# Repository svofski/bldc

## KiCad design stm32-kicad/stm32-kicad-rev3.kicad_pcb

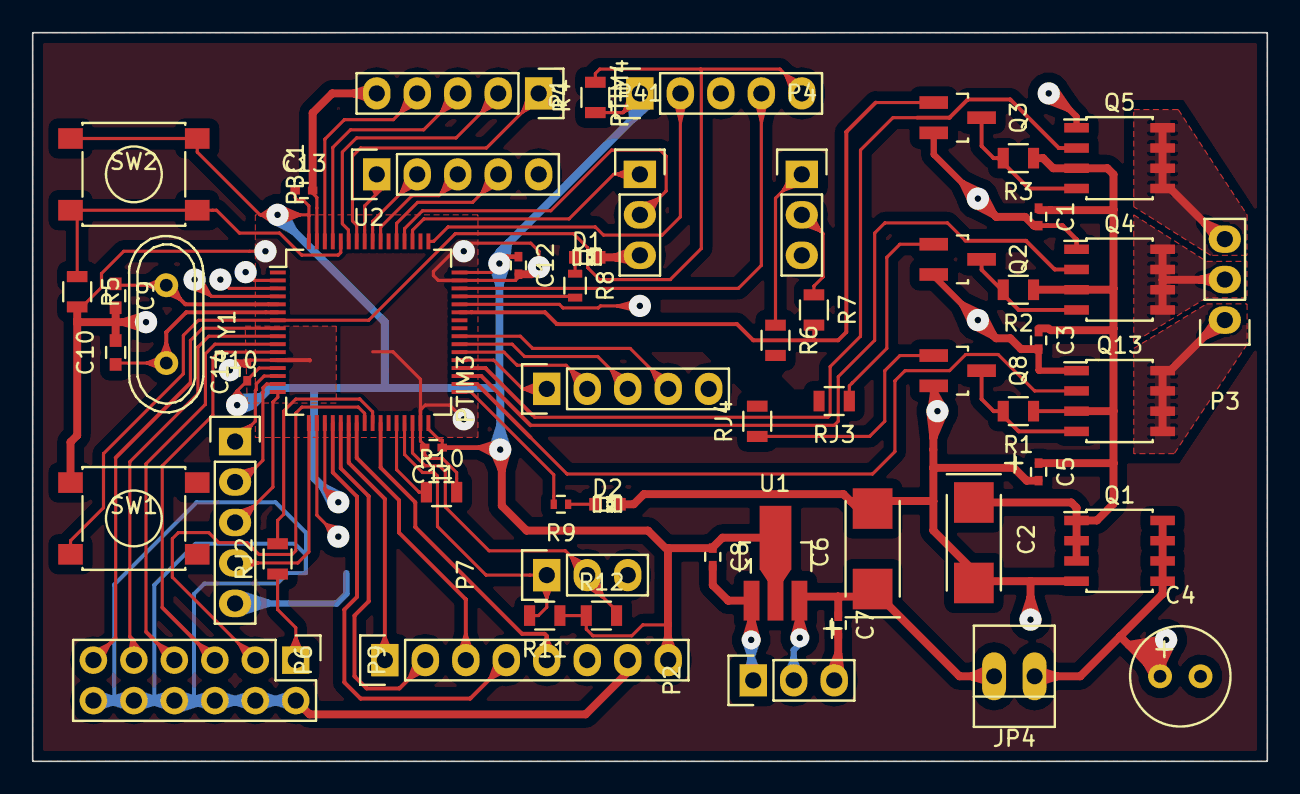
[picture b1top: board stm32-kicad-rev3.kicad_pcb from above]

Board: 2 copper layers, 77.5 x 45.7 mm, 57 parts (1 on the bottom side), 65 nets.

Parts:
C1, C3, C5, C7, C8, C11, C12, C13, C14: 0.1; C_0402
C2: 10.0; TantalC_SizeC_EIA-6032_Reflow
C4: 4.7; Elko_vert_11.2x6.3mm_RM2.5_CopperClear
C6: 10; TantalC_SizeC_EIA-6032_Reflow
C9, C10: 20; C_0603
D1, D2: LED; LED-0603
JP4: Jumper_NO_Small; PINHEAD1-2
P1, P10: CONN_01X05; Pin_Header_Straight_1x05
P2, P3, P4, P7, P41: CONN_01X03; Pin_Header_Straight_1x03
P6: CONN_01X08; Pin_Header_Straight_1x08
P9: CONN_02X06; Pin_Header_Straight_2x06
PBC1: CONN_01X05; Pin_Header_Straight_1x05
PTIM3, PTIM4: CONN_01X05; Pin_Header_Straight_1x05
Q1: FDS6675; SOIC-8_3.9x4.9mm_Pitch1.27mm
Q2, Q3, Q8: IRLML2502; SOT-23_Handsoldering
Q4, Q5, Q13: IRF7343PBF; SOIC-8_3.9x4.9mm_Pitch1.27mm
R1, R2, R3: 330; R_0805
R4, R5, R10: 10K; R_0805
R6, R7: 1K; R_0805
R8: 330; R_0603
R9: 330; R_0402
R11, R12: 4K7; R_0805
RJ1: 0; R_0402
RJ2, RJ3, RJ4: 0; R_0805
SW1, SW2: SW_PUSH; SW_SPST_PTS645
U1: NCP1117ST18T3G; SOT89-3_Housing_Handsoldering
U2: STM32F103RB; LQFP-64_10x10mm_Pitch0.5mm-nokeepout
Y1: 8MHz; Crystal_HC49-U_Vertical

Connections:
+3.3VP: C8.1, C11.1, C12.1, C13.1, C14.1, P1.1, P6.8, R4.1, R11.1, R12.1, SW2.1, U1.2, U2.13, U2.19, U2.32, U2.48, U2.64
+12V: C6.1, C7.1, JP4.2, P2.2, U1.3
/MOTORA: P3.1, Q13.5, Q13.6, Q13.7, Q13.8
/MOTORB: P3.2, Q4.5, Q4.6, Q4.7, Q4.8
/MOTORC: P3.3, Q5.5, Q5.6, Q5.7, Q5.8
/STM32/ADNS_MOT: P6.5, U2.26
/STM32/ANAL1: P9.11, U2.8
/STM32/ANAL2: P9.9, U2.9
/STM32/ANAL3: P9.7, U2.10
/STM32/ANAL4: P9.5, U2.11
/STM32/ANAL5: P9.3, U2.24
/STM32/ANAL6: RJ2.2, U2.25
/STM32/ANAL6x: P9.1, RJ2.1
/STM32/LED1: R9.2, U2.33
/STM32/LED2: R8.2, U2.45
/STM32/M1A: Q8.1, RJ4.1
/STM32/M1B: Q2.1, RJ3.1
/STM32/M1B_0: R6.2, RJ3.2, U2.42
/STM32/M1C: Q3.1, R7.2, U2.43
/STM32/PB3: PBC1.3, U2.55
/STM32/PB4: PBC1.2, U2.56
/STM32/PB5: PBC1.1, U2.57
/STM32/PC12: PBC1.4, U2.53
/STM32/RXD3: P41.2, U2.52
/STM32/SCL: P7.1, R11.2, U2.29
/STM32/SDA: P7.2, R12.2, U2.30
/STM32/SPI1_MISO: P6.1, U2.22
/STM32/SPI1_MOSI: P6.3, U2.23
/STM32/SPI1_SCK: P6.2, U2.21
/STM32/SWDCLK: P1.2, U2.49
/STM32/SWDIO: P1.4, U2.46
/STM32/TIM2_1: P10.1, U2.14
/STM32/TIM2_2: P10.2, U2.15
/STM32/TIM2_3: P10.3, U2.16
/STM32/TIM2_4: P10.4, U2.17
/STM32/TIM3_1: PTIM3.1, U2.37
/STM32/TIM3_2: PTIM3.2, U2.38
/STM32/TIM3_3: PTIM3.3, U2.39
/STM32/TIM3_4: PTIM3.4, U2.40
/STM32/TIM4_1: PTIM4.1, U2.58
/STM32/TIM4_2: PTIM4.2, U2.59
/STM32/TIM4_3: PTIM4.3, U2.61
/STM32/TIM4_4: PTIM4.4, U2.62
/STM32/TXD3: P41.1, U2.51
/STM32/~ADNS_CS: P6.4, U2.20
/STM32/~M1A: Q13.2, U2.34
/STM32/~M1B: Q4.2, U2.35
/STM32/~M1C: Q5.2, U2.36
/STM32/~RESET: P1.5, R4.2, SW1.2, U2.7
/VMOT: C1.1, C2.1, C3.1, C5.1, Q1.1, Q1.2, Q1.3, Q4.3, Q5.3, Q13.3, R1.1, R2.1, R3.1
GND: C1.2, C2.2, C3.2, C4.2, C5.2, C6.2, C7.2, C8.2, C9.2, C10.2, C11.2, C12.2, C13.2, D1.2, D2.2, P1.3, P2.1, P2.3, P4.3, P6.6, P7.3, P10.5, P41.3, PBC1.5, PTIM3.5, PTIM4.5, Q1.4, Q2.2, Q3.2, Q4.1, Q5.1, Q8.2, Q13.1, R5.2, R10.2, RJ1.2, SW1.1, U1.1, U2.18, U2.31, U2.47, U2.63
GNDA: C14.2, P6.7, P9.2, P9.4, P9.6, P9.8, P9.10, P9.12, RJ1.1, U2.12
unnamed: C4.1, JP4.1, Q1.5, Q1.6, Q1.7, Q1.8
unnamed: C9.1, U2.5, Y1.1
unnamed: C10.1, U2.6, Y1.2
unnamed: D1.1, R8.1
unnamed: D2.1, R9.1
unnamed: P4.1, R6.1
unnamed: P4.2, R7.1
unnamed: Q2.3, Q4.4, R2.2
unnamed: Q3.3, Q5.4, R3.2
unnamed: Q8.3, Q13.4, R1.2
unnamed: R5.1, SW2.2, U2.60
unnamed: R10.1, U2.28
unnamed: RJ4.2, U2.41

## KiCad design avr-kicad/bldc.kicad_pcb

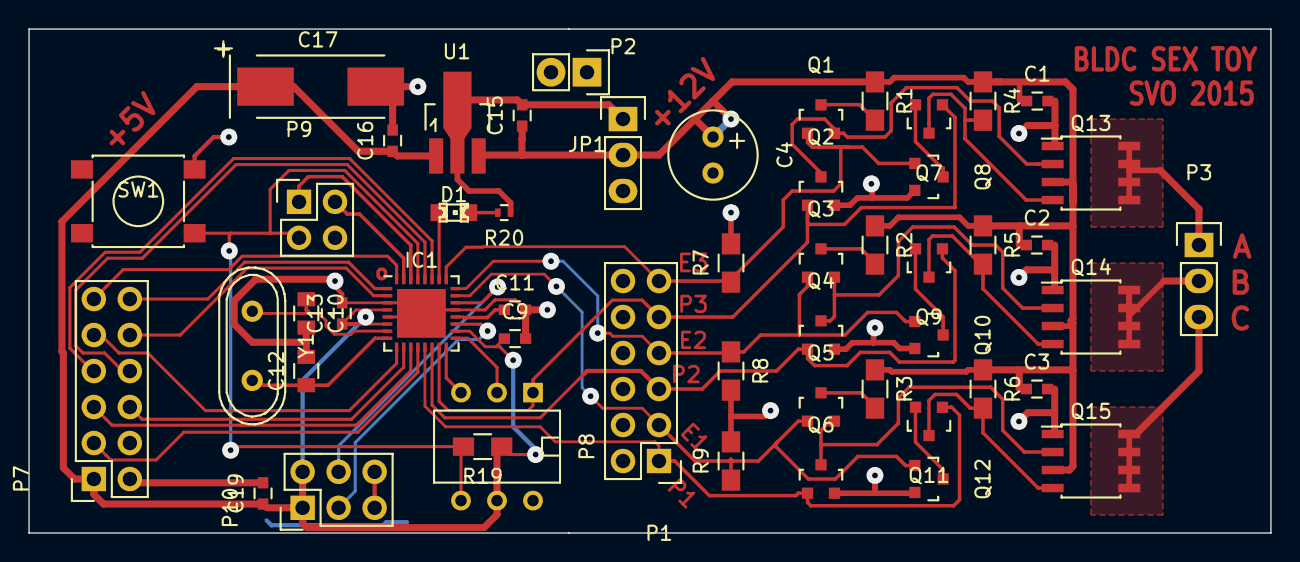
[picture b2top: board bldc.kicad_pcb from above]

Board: 2 copper layers, 87.6 x 35.6 mm, 52 parts (0 on the bottom side), 46 nets.

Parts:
C1, C2, C3, C9, C11, C13, C15, C16, C19: 0.1; C_0603
C4: 4.7; Elko_vert_11.2x6.3mm_RM2.5_CopperClear
C10, C12: 20; C_0805
C17: 10.0; TantalC_SizeD_EIA-7343_HandSoldering
D1: Led_Small; LED-0805
IC1: ATMEGA8-MI; QFN-32-1EP_5x5mm_Pitch0.5mm
JP1: Jumper_NO_Small; Socket_Strip_Straight_1x02
P1: CONN_02X06; Pin_Header_Straight_2x06
P2, P3: CONN_01X03; Pin_Header_Straight_1x03
P7: CONN_02X06; Socket_Strip_Straight_2x06
P8: CONN_01X06; DIP-6__300
P9: CONN_01X04; Pin_Header_Straight_2x02
P10: CONN_02X03; Pin_Header_Straight_2x03
Q1, Q2, Q3, Q4, Q5, Q6, Q7, Q8, Q9, Q10, Q11, Q12: IRLML0100; SOT-23
Q13, Q14, Q15: IRF7343PBF; SOIC-8_3.9x4.9mm_Pitch1.27mm
R1, R2, R3, R4, R5, R6: 4K7; R_0805_HandSoldering
R7, R8, R9, R19: 10K; R_0805_HandSoldering
R20: R; R_0402
SW1: SW_PUSH; SW_SPST_PTS645
U1: MC78L05ACH; SOT89-3_Housing_Handsoldering
Y1: Crystal_Small; Crystal_HC49-U_Vertical

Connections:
+5V: C9.1, C13.1, C16.1, C17.1, C19.1, IC1.4, IC1.6, IC1.18, P7.1, P8.5, P10.1, P10.2, R19.1, U1.1
+12V: C1.1, C2.1, C3.1, C4.1, C15.1, P2.2, Q13.3, Q14.3, Q15.3, R1.1, R2.1, R3.1, R4.1, R5.1, R6.1, U1.3
/MOTOR1: P3.1, Q13.5, Q13.6, Q13.7, Q13.8
/MOTOR2: P3.2, Q14.5, Q14.6, Q14.7, Q14.8
/MOTOR3: P3.3, Q15.5, Q15.6, Q15.7, Q15.8
/atmega/AIN0: IC1.10, P7.6
/atmega/AIN1: IC1.11, P7.5
/atmega/ENABLE1: IC1.23, P1.3, Q5.1, Q12.1, R9.1
/atmega/ENABLE2: IC1.24, P1.7, Q3.1, Q10.1, R8.1
/atmega/ENABLE3: IC1.25, P1.11, Q1.1, Q8.1, R7.1
/atmega/HALL1: IC1.19, P10.3
/atmega/HALL2: IC1.22, P10.4
/atmega/ICP: IC1.12, P7.3
/atmega/IRQ0: IC1.32, P7.11
/atmega/IRQ1: IC1.1, P7.12
/atmega/LED: D1.1, IC1.26
/atmega/MISO: IC1.16, P8.3
/atmega/PD4: IC1.2, P7.10
/atmega/PD5: IC1.9, P7.9
/atmega/PWM1: IC1.13, P1.1, Q6.1, Q11.1
/atmega/PWM2: IC1.14, P1.5, Q4.1, Q9.1
/atmega/PWM3: IC1.15, P1.9, P8.1, Q2.1, Q7.1
/atmega/RXD: IC1.30, P9.1
/atmega/SCK: IC1.17, P8.2
/atmega/SCL: IC1.28, P7.8
/atmega/SDA: IC1.27, P7.7
/atmega/TXD: IC1.31, P9.2
/atmega/~RESET: IC1.29, P8.4, P9.3, R19.2, SW1.2
GND: C1.2, C2.2, C3.2, C4.2, C15.2, JP1.1, P2.1, P2.3, Q2.2, Q4.2, Q6.2, Q8.2, Q10.2, Q12.2, Q13.1, Q14.1, Q15.1, R7.2, R8.2, R9.2, R20.1, U1.2
GNDD: C9.2, C10.2, C11.2, C12.2, C13.2, C16.2, C17.2, C19.2, IC1.3, IC1.5, IC1.21, IC1.33, JP1.2, P7.2, P8.6, P9.4, P10.5, P10.6, SW1.1
unnamed: C10.1, IC1.7, Y1.1
unnamed: C11.1, IC1.20
unnamed: C12.1, IC1.8, Y1.2
unnamed: D1.2, R20.2
unnamed: Q1.2, Q2.3, Q13.2
unnamed: Q1.3, R1.2
unnamed: Q3.3, R2.2
unnamed: Q5.3, R3.2
unnamed: Q7.2, Q8.3
unnamed: Q9.2, Q10.3
unnamed: Q11.2, Q12.3
unnamed: Q11.3, Q15.4, R6.2
unnamed: Q7.3, Q13.4, R4.2
unnamed: Q3.2, Q4.3, Q14.2
unnamed: Q9.3, Q14.4, R5.2
unnamed: Q5.2, Q6.3, Q15.2

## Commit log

2015-04-26 BLDC and STM32 experiments sandbox
2015-04-26 bleh
2015-04-26 tabs
2015-05-03 + adns-9800 camera mode + quadrature encoder (simple software x4)
2015-05-19 just the current state, junk
2015-11-30 python camera viewer
2015-11-30 wtf reaallly
